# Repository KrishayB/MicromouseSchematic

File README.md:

# Mouse Schematic

KiCad PCB design for micromouse:

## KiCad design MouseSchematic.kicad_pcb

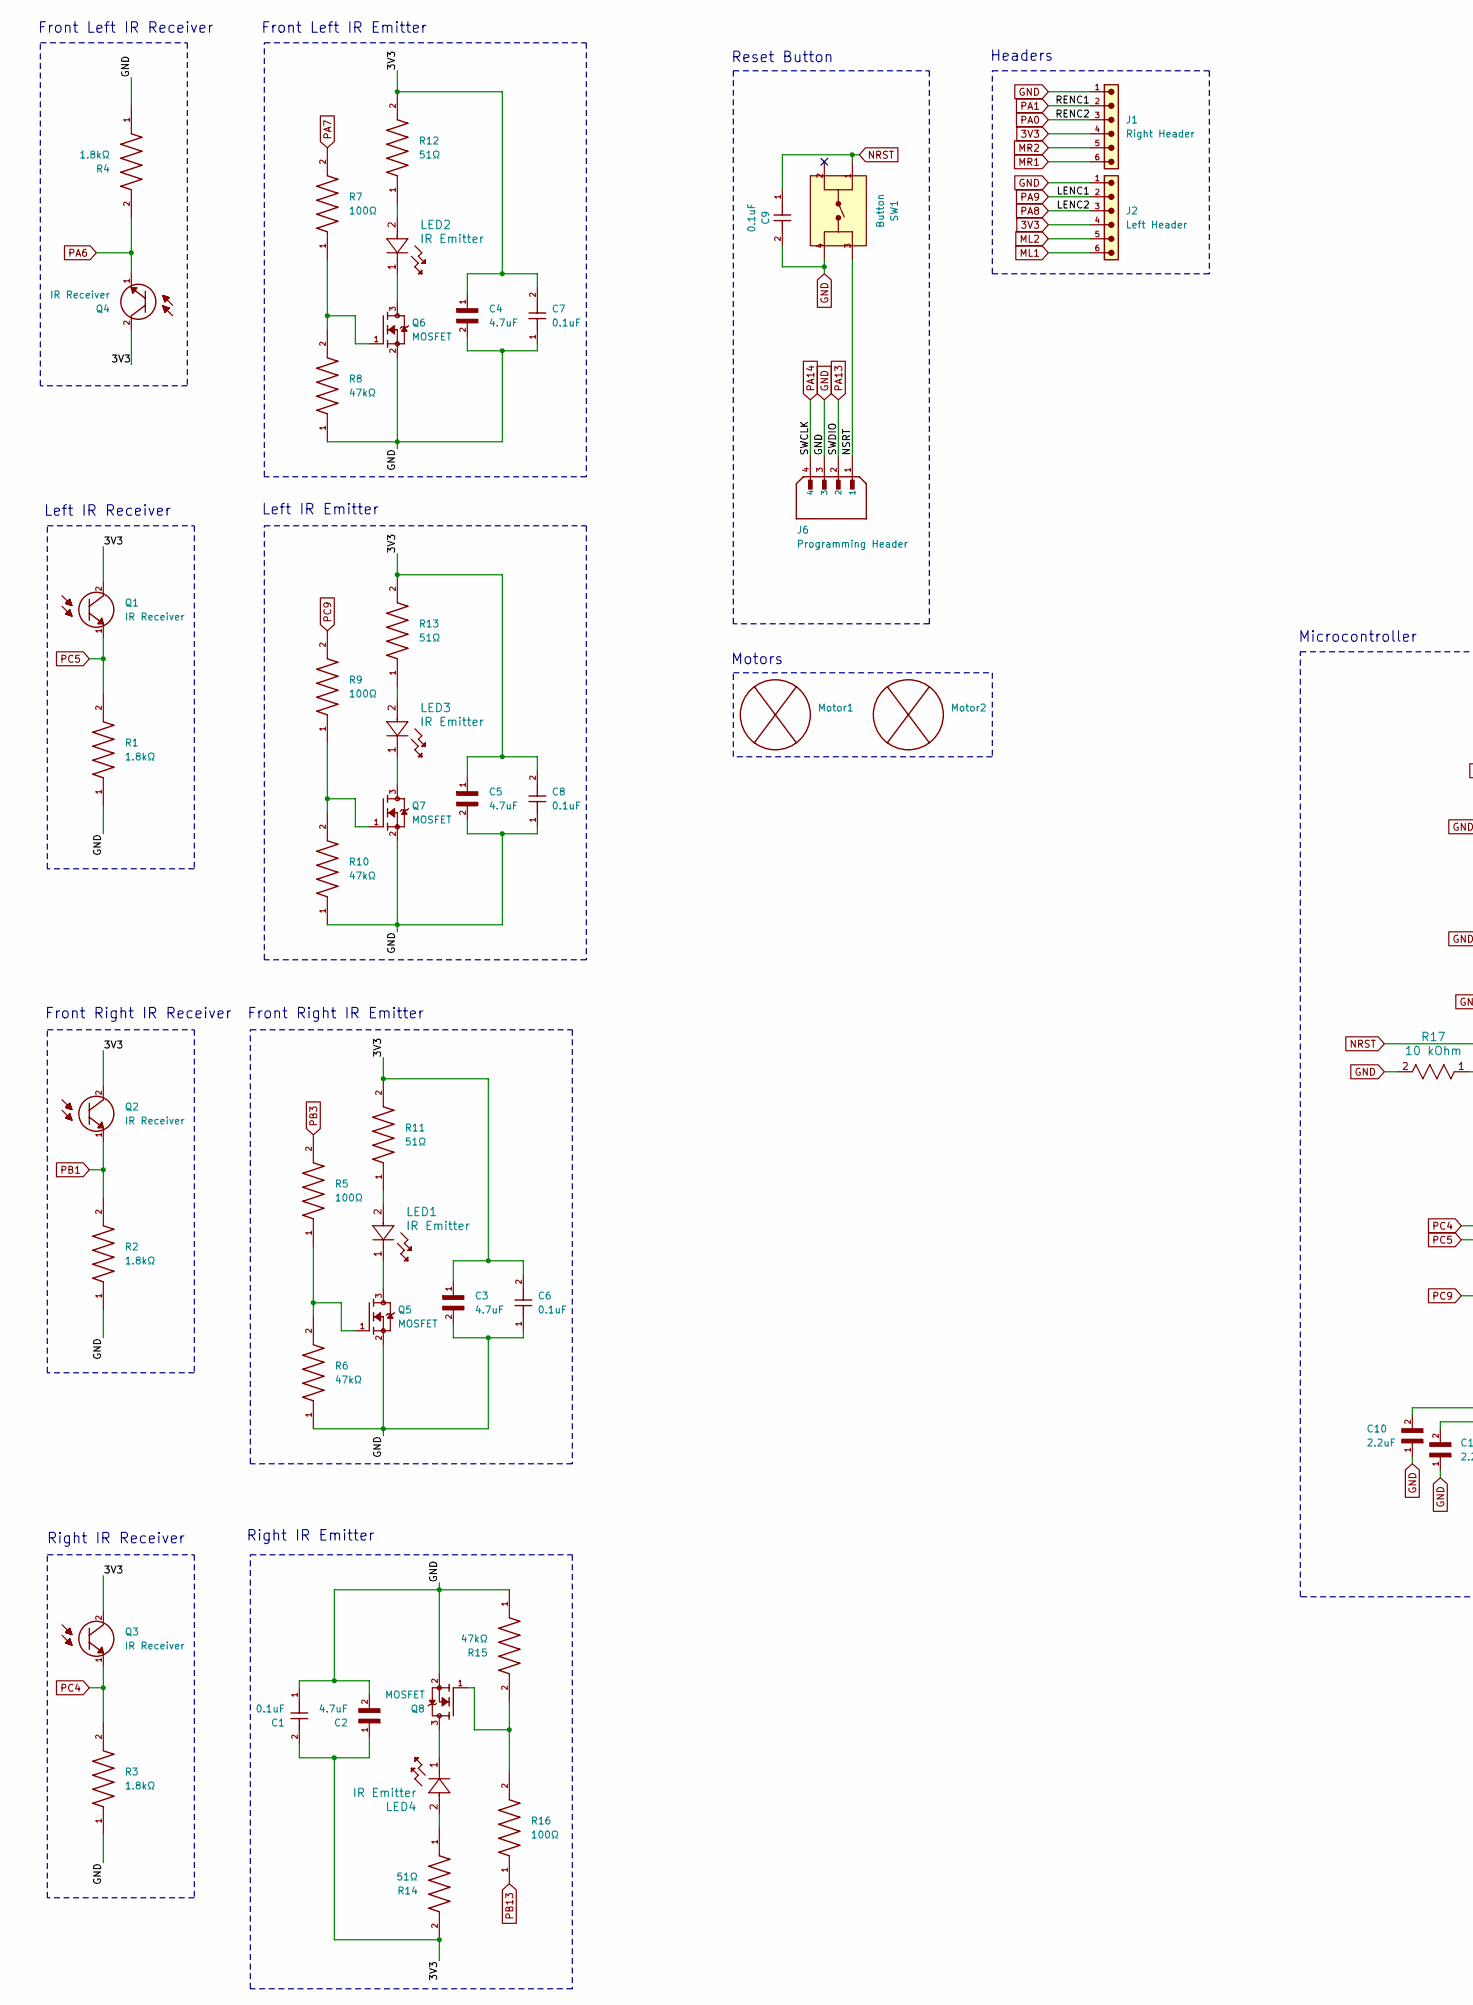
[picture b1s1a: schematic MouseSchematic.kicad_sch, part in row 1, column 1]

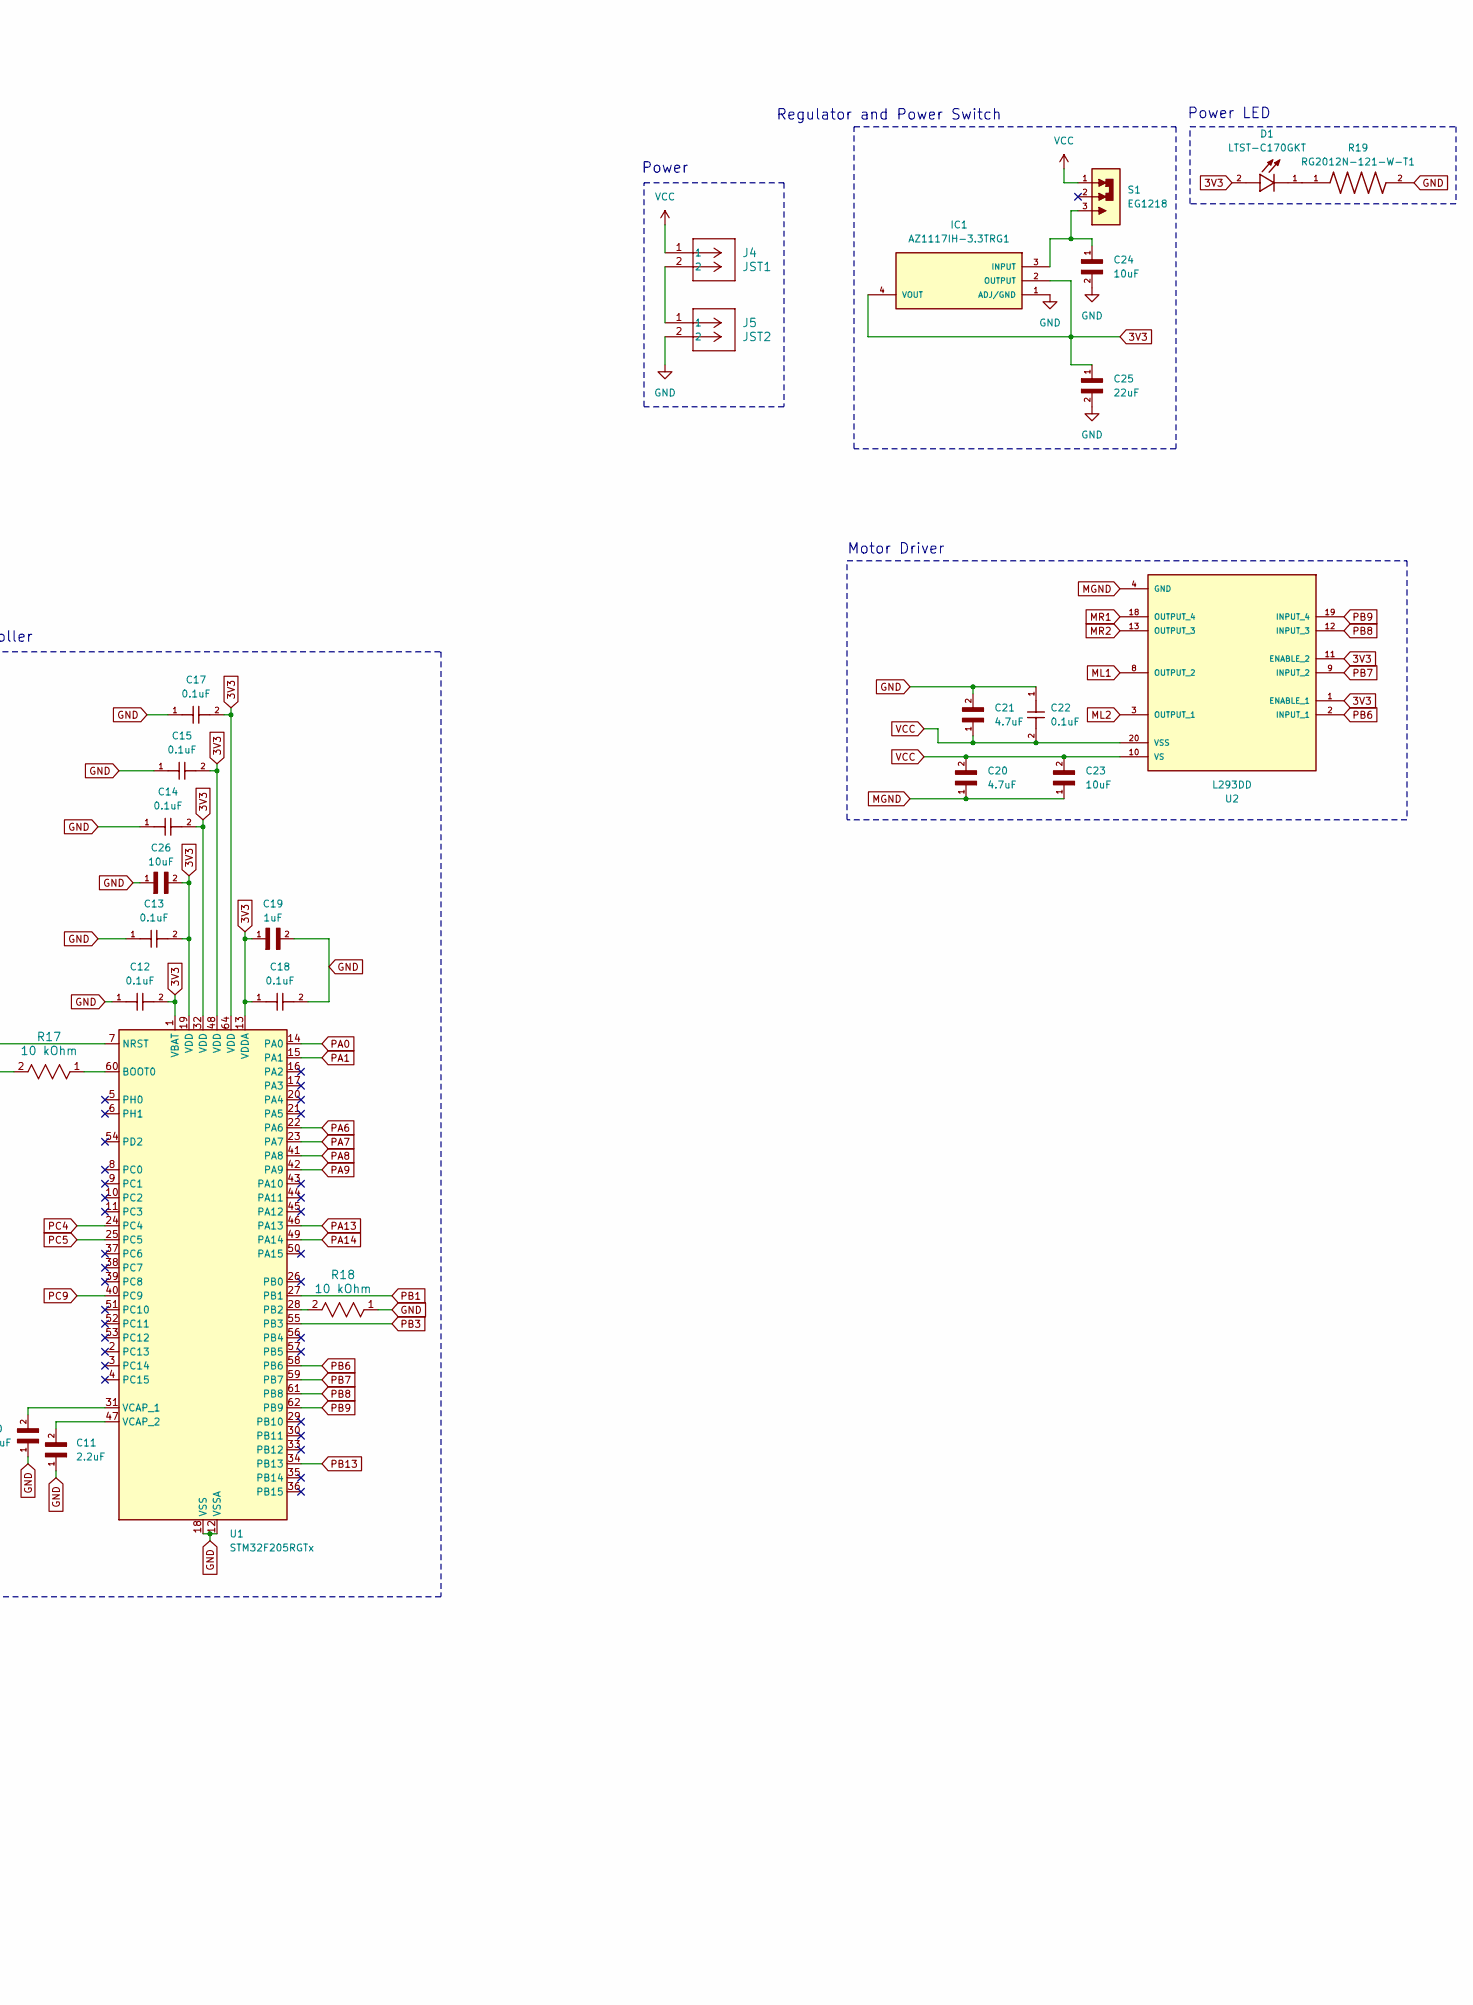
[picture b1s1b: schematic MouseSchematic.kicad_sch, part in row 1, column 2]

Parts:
C1, C6, C7, C8, C9, C12, C13, C14, C15, C17, C18, C22: 0.1uF; CAPC2012X88N
C2, C3, C4, C5, C20, C21: 4.7uF; CAPC2012X150N; DigiKey_Part_Number 445-8893-1-ND
C10, C11: 2.2uF; CAPC2012X135N; DigiKey_Part_Number 1276-2954-1-ND
C19: 1uF; CAPC2012X135N; DigiKey_Part_Number 1276-1029-1-ND
C23, C24, C26: 10uF; CAPC2012X140N; DigiKey_Part_Number 1276-2872-1-ND
C25: 22uF; CAPC2012X145N; DigiKey_Part_Number 1276-CL21A226MAYNNNECT-ND
D1: LTST-C170GKT; LED_LTST-C170GKT; PARTREV I; DigiKey_Part_Number 160-1179-1-ND
IC1: AZ1117IH-3.3TRG1; SOT230P700X170-4N; MOUSER_PART_NUMBER 621-AZ1117IH-3.3TRG1
J1: Right Header; 61300611121; DigiKey_Part_Number 732-5319-ND
J2: Left Header; 61300611121; DigiKey_Part_Number 732-5319-ND
J4: JST1; CONN2_B2B-PH-K-S_JST
J5: JST2; CONN2_B2B-PH-K-S_JST
J6: Programming Header; JST_B4B-XH-A; PARTREV 7/4/21; DigiKey_Part_Number 455-B4B-XH-A-ND
LED1, LED2, LED3, LED4: IR Emitter; LED_INL-5AMIR15_INO
Motor1, Motor2: Pololu_Motor
Q1, Q2, Q3, Q4: IR Receiver; XDCR_SFH_313_FA-3_4; PARTREV 1.3; DigiKey_Part_Number 475-SFH313FA-3/4-ND
Q5, Q6, Q7, Q8: MOSFET; SOT95P240X111-3N; PARTREV 4; DigiKey_Part_Number 2N7002LT1GOSCT-ND
R1, R2, R3, R4: 1.8kΩ; RESC2012X65N; DigiKey_Part_Number RMCF0805JT1K80CT-ND
R5, R7, R9, R16: 100Ω; RESC2012X50N; DigiKey_Part_Number 541-100CCT-ND
R6, R8, R10, R15: 47kΩ; RES_ERA6AEB473V; PARTREV 3/1/2020
R11, R12, R13, R14: 51Ω; RESC2012X60N
R17, R18: 10 kOhm; RESC2012X60N
R19: RG2012N-121-W-T1; RESC2012X50N; DigiKey_Part_Number RG20N120WCT-ND
S1: EG1218; SW_EG1218; DigiKey_Part_Number EG1903-ND
SW1: Button; TE_FSM4JSMA; PARTREV V
U1: STM32F205RGTx; LQFP-64_10x10mm_P0.5mm
U2: L293DD; SOIC127P1032X265-20N; PARTREV N/A; DigiKey_Part_Number 497-1390-5-ND

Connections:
3V3: C1.2, C2.1, C3.1, C4.1, C5.1, C6.2, C7.2, C8.2, C12.2, C13.2, C14.2, C15.2, C17.2, C18.1, C19.1, C25.1, C26.2, D1.2, IC1.2 (OUTPUT), IC1.4 (VOUT), J1.4, J2.4, Q1.2, Q2.2, Q3.2, Q4.2, R11.2, R12.2, R13.2, R14.2, U1.1 (VBAT), U1.13 (VDDA), U1.19 (VDD), U1.32 (VDD), U1.48 (VDD), U1.64 (VDD), U2.1 (ENABLE_1), U2.11 (ENABLE_2)
/NSRT: J6.1, SW1.3
GND: C1.1, C2.2, C3.2, C4.2, C5.2, C6.1, C7.1, C8.1, C9.2, C10.1, C11.1, C12.1, C13.1, C14.1, C15.1, C17.1, C18.2, C19.2, C21.2, C22.1, C24.2, C25.2, C26.1, IC1.1 (ADJ/GND), J1.1, J2.1, J5.2, J6.3, Q5.2, Q6.2, Q7.2, Q8.2, R1.1, R2.1, R3.1, R4.1, R6.1, R8.1, R10.1, R15.1, R17.2, R18.1, R19.2, SW1.4, U1.12 (VSSA), U1.18 (VSS), U1.63 (VSS)
MGND: C20.1, C23.1, U2.4 (GND), U2.5 (GND), U2.6 (GND), U2.7 (GND), U2.14 (GND), U2.15 (GND), U2.16 (GND), U2.17 (GND)
ML1: J2.6, U2.8 (OUTPUT_2)
ML2: J2.5, U2.3 (OUTPUT_1)
MR1: J1.6, U2.18 (OUTPUT_4)
MR2: J1.5, U2.13 (OUTPUT_3)
NRST: C9.1, SW1.1, U1.7 (NRST)
unnamed: D1.1, R19.1
unnamed: C24.1, IC1.3 (INPUT), S1.3
unnamed: J4.2, J5.1
unnamed: LED1.1, Q5.3
unnamed: LED1.2, R11.1
unnamed: LED2.1, Q6.3
unnamed: LED2.2, R12.1
unnamed: LED3.1, Q7.3
unnamed: LED3.2, R13.1
unnamed: LED4.1, Q8.3
unnamed: LED4.2, R14.1
unnamed: Q5.1, R5.1, R6.2
unnamed: Q6.1, R7.1, R8.2
unnamed: Q7.1, R9.1, R10.2
unnamed: Q8.1, R15.2, R16.2
unnamed: R17.1, U1.60 (BOOT0)
unnamed: R18.2, U1.28 (PB2)
unnamed: C10.2, U1.31 (VCAP_1)
unnamed: C11.2, U1.47 (VCAP_2)
PA0: J1.3, U1.14 (PA0)
PA1: J1.2, U1.15 (PA1)
PA6: Q4.1, R4.2, U1.22 (PA6)
PA7: R7.2, U1.23 (PA7)
PA8: J2.3, U1.41 (PA8)
PA9: J2.2, U1.42 (PA9)
PA13: J6.2, U1.46 (PA13)
PA14: J6.4, U1.49 (PA14)
PB1: Q2.1, R2.2, U1.27 (PB1)
PB3: R5.2, U1.55 (PB3)
PB6: U1.58 (PB6), U2.2 (INPUT_1)
PB7: U1.59 (PB7), U2.9 (INPUT_2)
PB8: U1.61 (PB8), U2.12 (INPUT_3)
PB9: U1.62 (PB9), U2.19 (INPUT_4)
PB13: R16.1, U1.34 (PB13)
PC4: Q3.1, R3.2, U1.24 (PC4)
PC5: Q1.1, R1.2, U1.25 (PC5)
PC9: R9.2, U1.40 (PC9)
VCC: C20.2, C21.1, C22.2, C23.2, J4.1, S1.1, U2.10 (VS), U2.20 (VSS)

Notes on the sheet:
Reset Button
Front Left IR Emitter
Front Left IR Receiver
Front Right IR Emitter
Right IR Receiver
Power LED
Left IR Receiver
Regulator and Power Switch
Front Right IR Receiver
Motors
Left IR Emitter
Motor Driver
Right IR Emitter
Microcontroller
Power
Headers

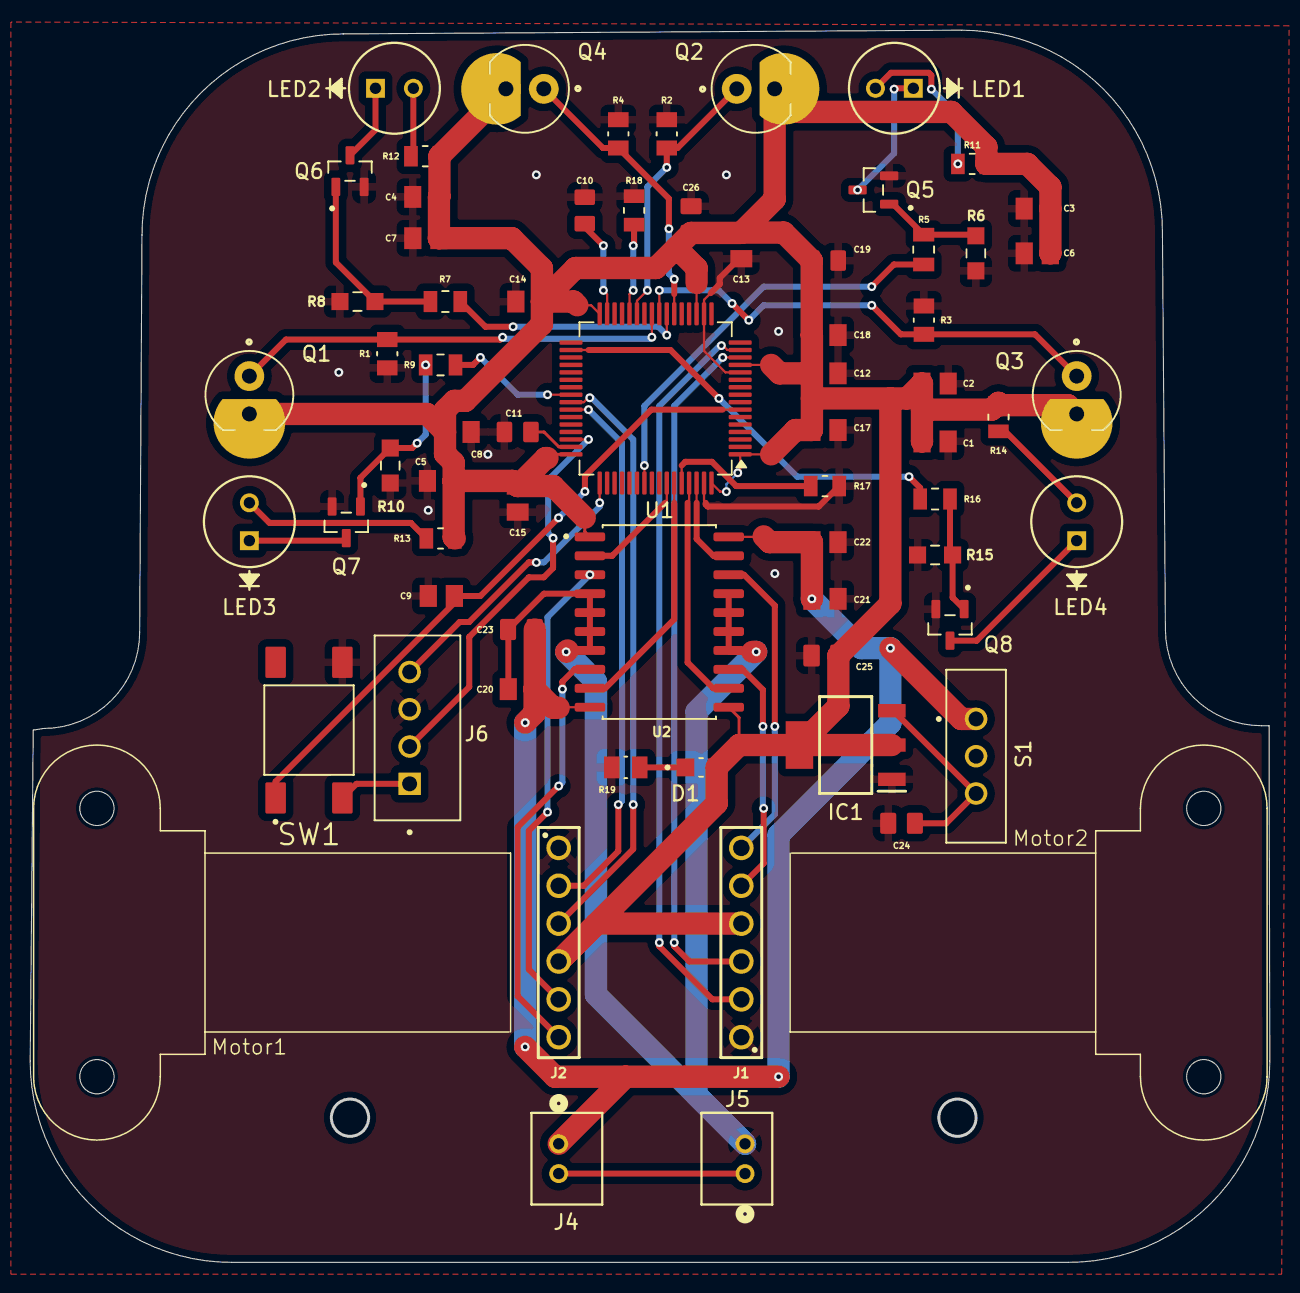
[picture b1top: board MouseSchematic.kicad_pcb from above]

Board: 2 copper layers, 83.0 x 82.5 mm, 69 parts (0 on the bottom side), 47 nets.

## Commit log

2026-01-25 Added microcontroller, organized
2026-01-25 Finished schematic wiring
2026-01-30 Schematic review
2026-01-30 Update schematic with more global labels (still need to finish reviewing)
2026-02-05 Added power LED, updated certain resistors and capacitors to match requirements
2026-02-17 Updated all footprints
2026-03-02 Started layout (laid out 1 IR sensor/emitter pair, motor driver, and put components in general location)
2026-03-04 Added 2nd IR sensor emitter pair
2026-03-04 Finished main layout of components still need to finish final touches and traces
2026-03-05 Added traces but now gotta move components a little further apart from each other to make room for fill zones
2026-03-05 Redo main layout and add motor footprints
2026-03-05 Added power traces
2026-03-05 Added copper layers and finished board layout
2026-03-07 Finished PCB with MGND issue fixed and edge cuts for battery holders
2026-03-07 Fixed error in schematic with incorrect MGND label
2026-03-09 Final PCB
